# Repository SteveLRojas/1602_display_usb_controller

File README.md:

# 1602_display_usb_controller
Small controller board for 1602, 2004 and similar displays. It is intended to be controlled by a python script.

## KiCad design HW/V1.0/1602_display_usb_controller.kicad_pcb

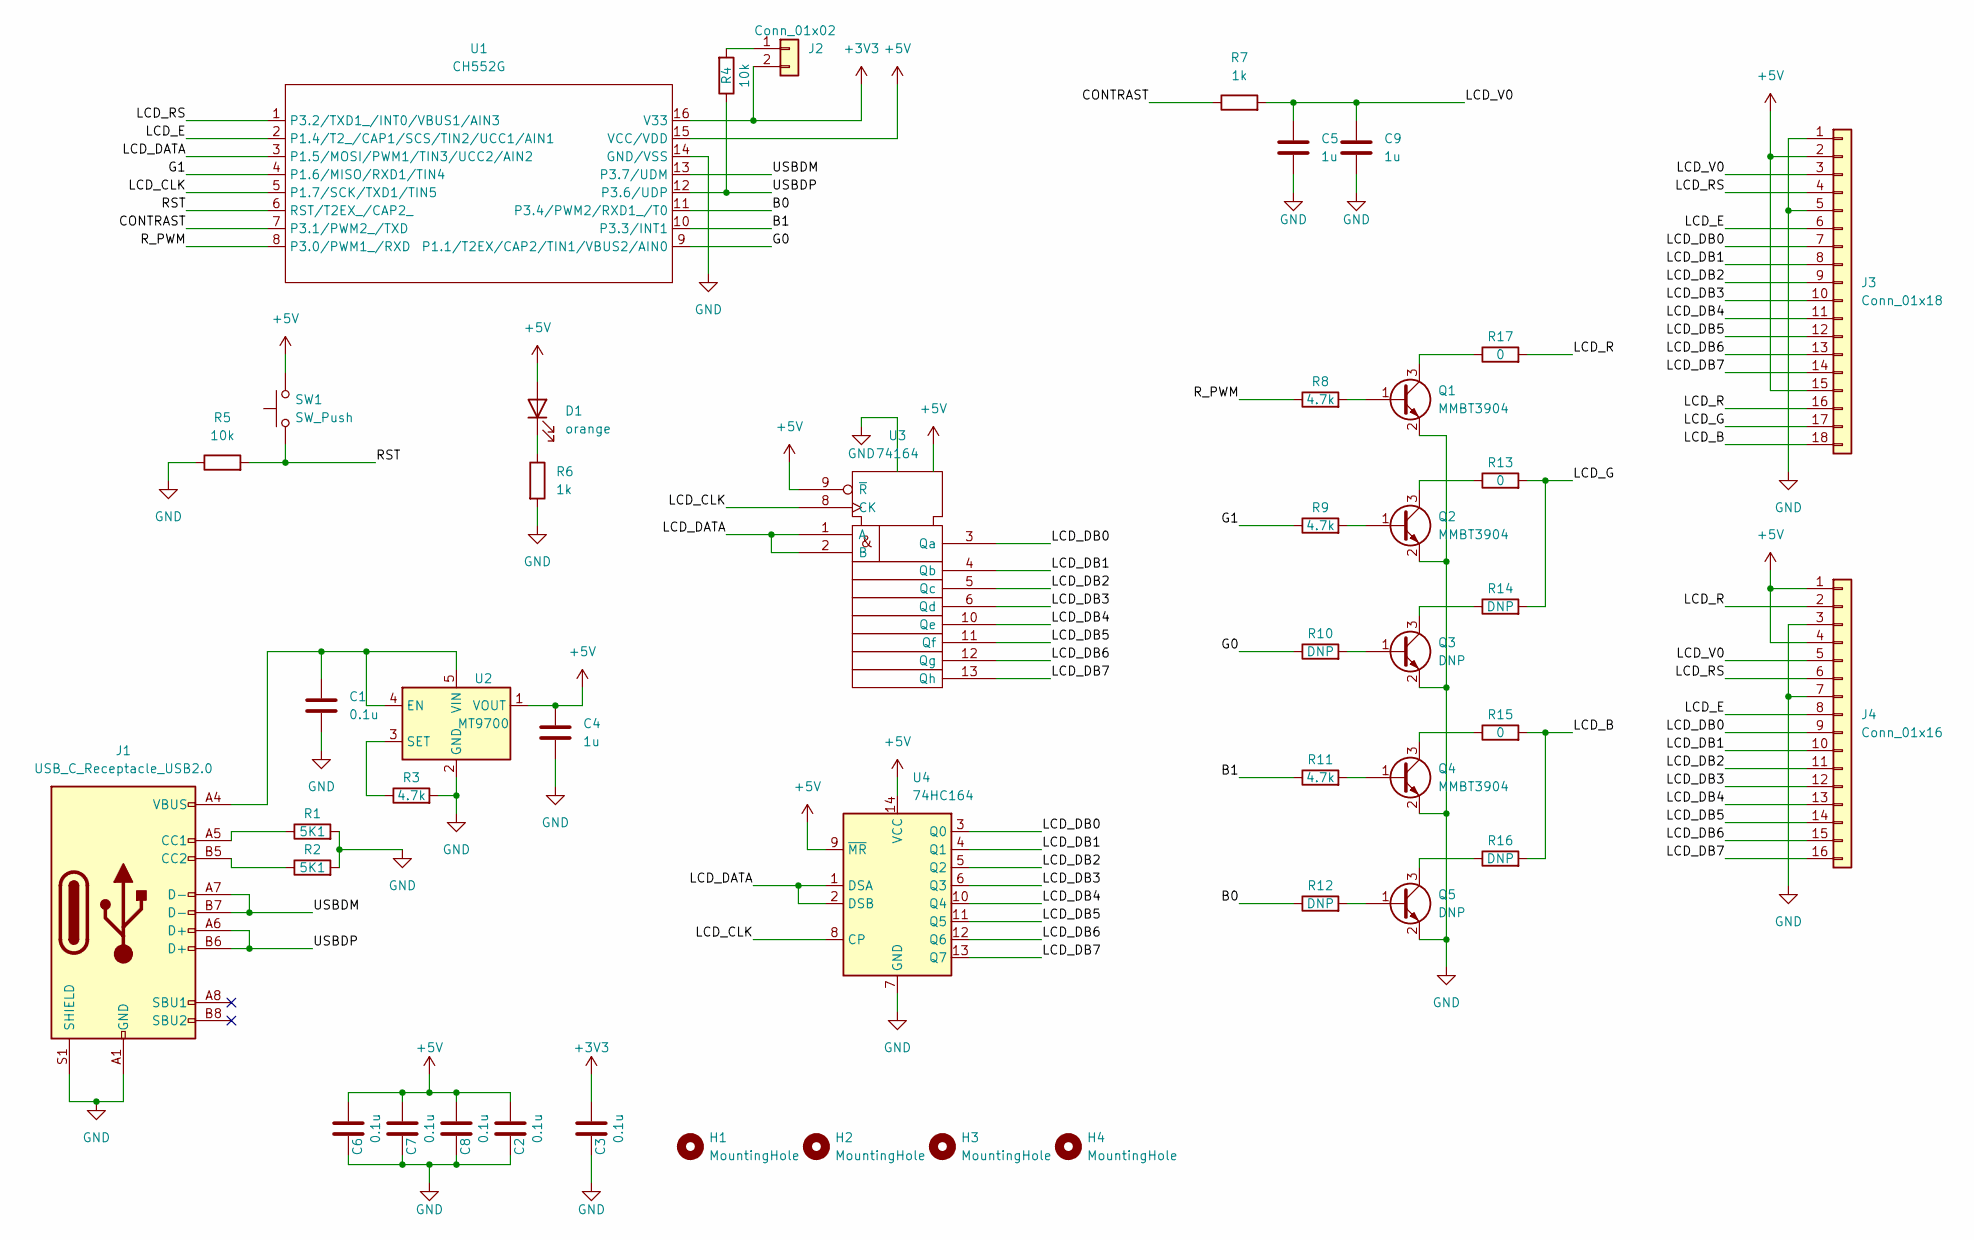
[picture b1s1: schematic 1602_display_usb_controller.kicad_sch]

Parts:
C1, C2, C3, C6, C7, C8: 0.1u; C_0805_2012Metric
C4, C5, C9: 1u; C_0805_2012Metric
D1: orange; LED_0805_2012Metric
H1, H2, H3, H4: MountingHole; MountingHole_2.5mm
J1: USB_C_Receptacle_USB2.0; USB_C_Receptacle_HRO_TYPE-C-31-M-12
J2: Conn_01x02; PinHeader_1x02_P1.27mm_Vertical
J3: Conn_01x18; PinSocket_1x18_P2.54mm_Vertical
J4: Conn_01x16; PinSocket_1x16_P2.54mm_Vertical
Q1, Q2, Q4: MMBT3904; SOT-23
Q3, Q5: DNP; SOT-23
R1, R2: 5K1; R_0805_2012Metric
R3, R8, R9, R11: 4.7k; R_0805_2012Metric
R4, R5: 10k; R_0805_2012Metric
R6, R7: 1k; R_0805_2012Metric
R10, R12, R14, R16: DNP; R_0805_2012Metric
R13, R15, R17: 0; R_0805_2012Metric
SW1: SW_Push; SW_SPST_PTS810
U1: CH552G; SO-16_3.9x9.9mm_P1.27mm
U2: MT9700; SOT-23-5
U3: 74164; DIP-14_W7.62mm
U4: 74HC164; SO-14_3.9x8.65mm_P1.27mm

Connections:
+3V3: C3.1, J2.2, U1.16 (V33)
+5V: C2.1, C4.1, C6.1, C7.1, C8.1, D1.2 (A), J3.2, J3.15, J4.1, J4.4, SW1.2, U1.15 (VCC/VDD), U2.1 (VOUT), U3.9 (~R), U3.14 (Vdd), U4.9 (~MR), U4.14 (VCC)
/B0: R12.1, U1.11 (P3.4/PWM2/RXD1_/T0)
/B1: R11.1, U1.10 (P3.3/INT1)
/CONTRAST: R7.1, U1.7 (P3.1/PWM2_/TXD)
/G0: R10.1, U1.9 (P1.1/T2EX/CAP2/TIN1/VBUS2/AIN0)
/G1: R9.1, U1.4 (P1.6/MISO/RXD1/TIN4)
/LCD_B: J3.18, R15.2, R16.2
/LCD_CLK: U1.5 (P1.7/SCK/TXD1/TIN5), U3.8 (CK), U4.8 (CP)
/LCD_DATA: U1.3 (P1.5/MOSI/PWM1/TIN3/UCC2/AIN2), U3.1 (A), U3.2 (B), U4.1 (DSA), U4.2 (DSB)
/LCD_DB0: J3.7, J4.9, U3.3 (Qa), U4.3 (Q0)
/LCD_DB1: J3.8, J4.10, U3.4 (Qb), U4.4 (Q1)
/LCD_DB2: J3.9, J4.11, U3.5 (Qc), U4.5 (Q2)
/LCD_DB3: J3.10, J4.12, U3.6 (Qd), U4.6 (Q3)
/LCD_DB4: J3.11, J4.13, U3.10 (Qe), U4.10 (Q4)
/LCD_DB5: J3.12, J4.14, U3.11 (Qf), U4.11 (Q5)
/LCD_DB6: J3.13, J4.15, U3.12 (Qg), U4.12 (Q6)
/LCD_DB7: J3.14, J4.16, U3.13 (Qh), U4.13 (Q7)
/LCD_E: J3.6, J4.8, U1.2 (P1.4/T2_/CAP1/SCS/TIN2/UCC1/AIN1)
/LCD_G: J3.17, R13.2, R14.2
/LCD_R: J3.16, J4.2, R17.2
/LCD_RS: J3.4, J4.6, U1.1 (P3.2/TXD1_/INT0/VBUS1/AIN3)
/LCD_V0: C5.1, C9.1, J3.3, J4.5, R7.2
/RST: R5.2, SW1.1, U1.6 (RST/T2EX_/CAP2_)
/R_PWM: R8.1, U1.8 (P3.0/PWM1_/RXD)
/USBDM: J1.A7 (D-), J1.B7 (D-), U1.13 (P3.7/UDM)
/USBDP: J1.A6 (D+), J1.B6 (D+), R4.1, U1.12 (P3.6/UDP)
GND: C1.2, C2.2, C3.2, C4.2, C5.2, C6.2, C7.2, C8.2, C9.2, J1.A1 (GND), J1.A12 (GND), J1.B1 (GND), J1.B12 (GND), J1.S1 (SHIELD), J3.1, J3.5, J4.3, J4.7, Q1.2 (E), Q2.2 (E), Q3.2 (E), Q4.2 (E), Q5.2 (E), R1.2, R2.2, R3.2, R5.1, R6.2, U1.14 (GND/VSS), U2.2 (GND), U3.7 (Vss), U4.7 (GND)
unnamed: C1.1, J1.A4 (VBUS), J1.A9 (VBUS), J1.B4 (VBUS), J1.B9 (VBUS), U2.4 (EN), U2.5 (VIN)
unnamed: D1.1 (K), R6.1
unnamed: J1.A5 (CC1), R1.1
unnamed: J1.B5 (CC2), R2.1
unnamed: J2.1, R4.2
unnamed: Q1.1 (B), R8.2
unnamed: Q1.3 (C), R17.1
unnamed: Q2.1 (B), R9.2
unnamed: Q2.3 (C), R13.1
unnamed: Q3.1 (B), R10.2
unnamed: Q3.3 (C), R14.1
unnamed: Q4.1 (B), R11.2
unnamed: Q4.3 (C), R15.1
unnamed: Q5.1 (B), R12.2
unnamed: Q5.3 (C), R16.1
unnamed: R3.1, U2.3 (SET)

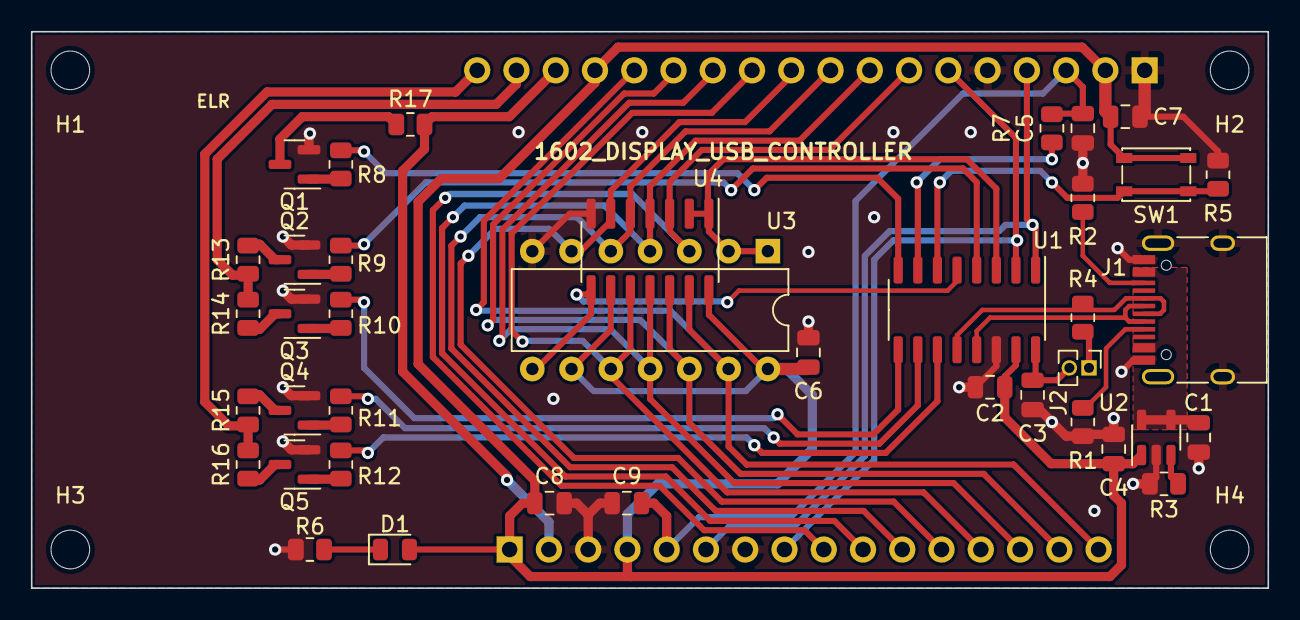
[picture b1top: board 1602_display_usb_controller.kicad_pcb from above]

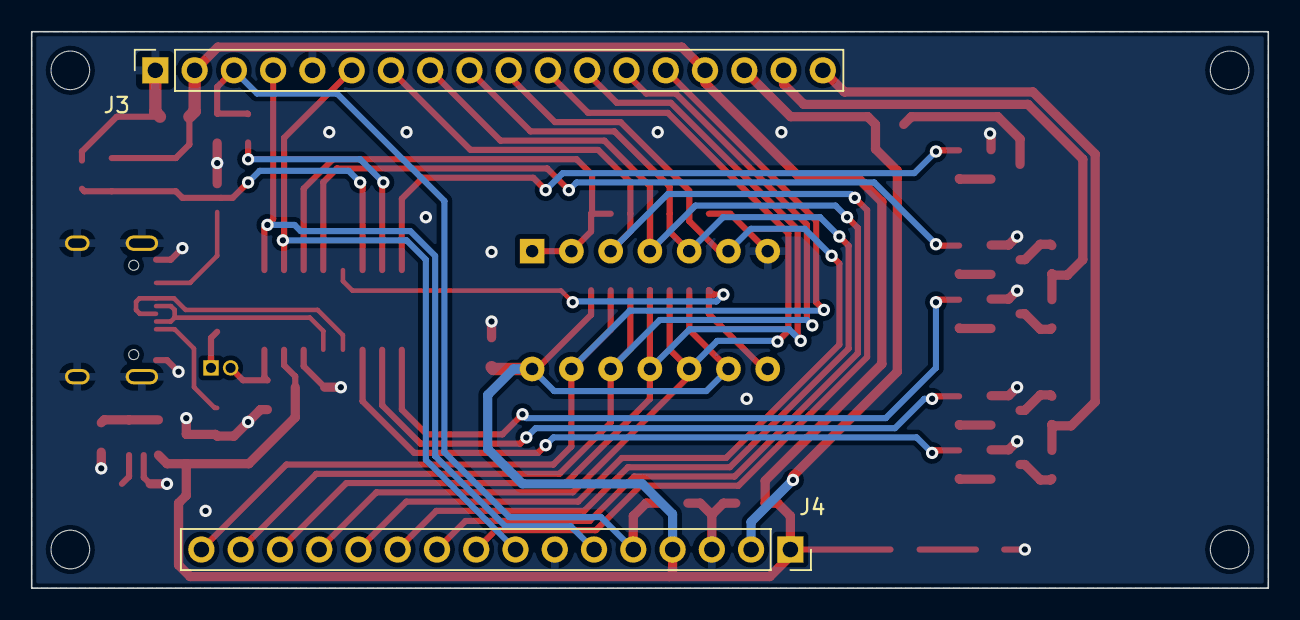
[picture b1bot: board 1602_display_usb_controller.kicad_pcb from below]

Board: 2 copper layers, 80.0 x 36.0 mm, 45 parts (2 on the bottom side), 44 nets.

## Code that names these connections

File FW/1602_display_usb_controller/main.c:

#include "CH552.H"
#include "CH552_RCC.h"
#include "CH552_TIMER.h"
#include "CH552_GPIO.h"
#include "CH552_PWM.h"
#include "CH552_USB_CDC.h"
#include "CH552_ST7066.h"

//Pins:
// LCD_E = P14
// LCD_DATA = P15
// G_PWM = P16
// LCD_CLK = P17
// R_PWM = P30
// LCD_CONTRAST = P31
// LCD_RS = P32
// B_PWM = P33
// UDP = P36
// UDM = P37

//PWM1 -> R_PWM
//PWM2 -> CONTRAST

int main()
{
	UINT8 prev_reset_typ;
	UINT16 com_wdog_count = 0;
	UINT16 com_wdog_limit = 0;
	
	UINT8 prev_control_line_state;
	UINT8 datagram[2];
	UINT16 bytes_available;
	UINT8 temp;
	UINT8 pwm_count = 0x08;
	
	UINT8 cursor_col = 0;
	UINT8 cursor_row = 0;
	UINT8 contrast = 45;
	UINT8 brightness_r = 127;
	UINT8 brightness_g = 127;
	UINT8 brightness_b = 127;
	UINT8 power_state = ST7066_DISP_ON_OFF_DISP_ON;
	
	rcc_set_clk_freq(RCC_CLK_FREQ_24M);
	
	gpio_set_mode(GPIO_MODE_PP, GPIO_PORT_1, GPIO_PIN_4 | GPIO_PIN_5 | GPIO_PIN_6 |GPIO_PIN_7);	//LCD_E, LCD_DATA, G_PWM, LCD_CLK
	gpio_set_mode(GPIO_MODE_PP, GPIO_PORT_3, GPIO_PIN_0 | GPIO_PIN_1 | GPIO_PIN_2 | GPIO_PIN_3);	//R_PWM, LCD_CONTRAST, LCD_RS, B_PWM
	gpio_clear_pin(GPIO_PORT_1, GPIO_PIN_4);
	gpio_clear_pin(GPIO_PORT_3, GPIO_PIN_2);
	
	pwm_init(PWM_1 | PWM_2, PWM_ACTIVE_HIGH, 1, PWM_1_P30 | PWM_2_P31);
	pwm_set_duty_cycle(PWM_1, brightness_r);
	pwm_set_duty_cycle(PWM_2, contrast);
	timer_init(TIMER_0, NULL);
	timer_set_period(TIMER_0, FREQ_SYS / 1000ul);	//period is 1ms
	EA = 1;	//enable interupts
	E_DIS = 0;
	
	prev_reset_typ = RESET_KEEP;
	RESET_KEEP = rcc_get_rst_typ();
	if((RESET_KEEP == RCC_RST_TYP_WDOG) || (RESET_KEEP == RCC_RST_TYP_SOFT))
	{
		rcc_delay_ms(500);
	}
	else
	{
		rcc_delay_ms(15);	//needed for some display modules
	}
	
	st7066_init();
	
	cdc_init();
	cdc_set_serial_state(CDC_SS_TXCARRIER | CDC_SS_RXCARRIER);
	prev_control_line_state = cdc_control_line_state;
	while(!cdc_config);
	
	timer_start(TIMER_0);
	
	rcc_reload_wdog(0x00);
	rcc_set_wdog_rst_en(RCC_WDOG_ENABLED);
	
	while(TRUE)
	{
		bytes_available = cdc_bytes_available();
		temp = cdc_peek();
		if((bytes_available >= 2) && (temp & 0x80))	//Handle write datagram
		{
			cdc_read_bytes(datagram, 2);
			
			switch(datagram[0] & 0x7F)
			{
				case 0x0A:
					cursor_col = datagram[1];
					st7066_set_cursor(cursor_row, cursor_col);
					break;
				case 0x0B:
					cursor_row = datagram[1];
					st7066_set_cursor(cursor_row, cursor_col);
					break;
				
				case 0x0C:
					contrast = datagram[1];
					pwm_set_duty_cycle(PWM_2, contrast);
					break;
				case 0x0D:
					brightness_r = datagram[1];
					pwm_set_duty_cycle(PWM_1, brightness_r);
					break;
				case 0x0E:
					brightness_g = datagram[1];
					break;
				case 0x0F:
					brightness_b = datagram[1];
					break;
				
				case 0x10:
					st7066_init();
					cursor_col = 0;
					cursor_row = 0;
					break;
				case 0x11:
					st7066_clear_display();
					cursor_col = 0;
					cursor_row = 0;
					break;
				case 0x12:
					cursor_col = 0;
					cursor_row = datagram[1];
					st7066_clear_line(cursor_row);
					break;
				case 0x13:
					st7066_write_char(datagram[1]);
					cursor_col += 1;
					break;
				
				case 0x14:
					power_state = datagram[1] & (ST7066_DISP_ON_OFF_DISP_ON | ST7066_DISP_ON_OFF_CURS_ON | ST7066_DISP_ON_OFF_BLINK_ON);
					st7066_send_command(ST7066_COM_DISP_ON_OFF | power_state);
					break;
				case 0x16:
					com_wdog_limit &= 0xFF00;
					com_wdog_limit |= datagram[1];
					break;
				case 0x17:
					com_wdog_limit &= 0x00FF;
					com_wdog_limit |= ((UINT16)datagram[1]) << 8;
					break;
				default: ;
			}
			
			com_wdog_count = 0;
		}
		else if(bytes_available && !(temp & 0x80))	//handle read datagram
		{
			datagram[0] = cdc_read_byte();
			
			switch(datagram[0])
			{
				case 0x00:	//device_id[0]
					datagram[0] = '1';
					break;
				case 0x01:	//device_id[1]
					datagram[0] = '6';
					break;
				case 0x02:	//device_id[2]
					datagram[0] = '0';
					break;
				case 0x03:	//device_id[3]
					datagram[0] = '2';
					break;
				
				case 0x04:	//unique_id[0]
					datagram[0] = (UINT8)(*(UINT16 code*)ROM_CHIP_ID_LO);
					break;
				case 0x05:	//unique_id[1]
					datagram[0] = (UINT8)((*(UINT16 code*)ROM_CHIP_ID_LO) >> 8);
					break;
				case 0x06:	//unique_id[2]
					datagram[0] = (UINT8)(*(UINT16 code*)ROM_CHIP_ID_HI);
					break;
				case 0x07:	//unique_id[3]
					datagram[0] = (UINT8)((*(UINT16 code*)ROM_CHIP_ID_HI) >> 8);
					break;
				
				case 0x08:
					datagram[0] = ST7066_NUM_COLUMNS;
					break;
				case 0x09:
					datagram[0] = ST7066_NUM_ROWS;
					break;
				case 0x0A:
					datagram[0] = cursor_col;
					break;
				case 0x0B:
					datagram[0] = cursor_row;
					break;
				
				case 0x0C:
					datagram[0] = contrast;
					break;
				case 0x0D:
					datagram[0] = brightness_r;
					break;
				case 0x0E:
					datagram[0] = brightness_g;
					break;
				case 0x0F:
					datagram[0] = brightness_b;
					break;
				
				case 0x14:
					datagram[0] = power_state;
					break;
				case 0x15:
					datagram[0] = prev_reset_typ | (RESET_KEEP >> 4);
					break;
				case 0x16:
					datagram[0] = (UINT8)com_wdog_limit;
					break;
				case 0x17:
					datagram[0] = (UINT8)(com_wdog_limit >> 8);
				default: ;
			}
			
			cdc_write_byte(datagram[0]);
			com_wdog_count = 0;
		}
		else if(bytes_available)	//datagrams not received in a single transfer are ignored
		{
			cdc_read_bytes(datagram, bytes_available);	//get rid of the extra bytes
		}
		
		if(com_wdog_limit && com_wdog_limit == com_wdog_count)
		{
			rcc_soft_reset();
		}
		
		if(timer_overflow_counts[TIMER_0])
		{
			timer_overflow_counts[TIMER_0] = 0;
			
			if(brightness_g >= pwm_count)
				gpio_set_pin(GPIO_PORT_1, GPIO_PIN_6);
			else
				gpio_clear_pin(GPIO_PORT_1, GPIO_PIN_6);
			
			if(brightness_b >= pwm_count)
				gpio_set_pin(GPIO_PORT_3, GPIO_PIN_3);
			else
				gpio_clear_pin(GPIO_PORT_3, GPIO_PIN_3);
			
			pwm_count += 0x10;
			com_wdog_count += 1;
		}
		
		if(prev_control_line_state != cdc_control_line_state)
		{
			cdc_set_serial_state(cdc_control_line_state & 3);
			prev_control_line_state = cdc_control_line_state;
		}
		
		rcc_reload_wdog(0x00);
	}
}

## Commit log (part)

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2026-03-12 Added design files
2026-03-17 Fixed CDC bug, added com watchdog, improvements in python files
2026-03-20 Added python scripts
2026-03-21 Added test scripts
2026-05-18 Added cpu and mem usage script
2026-06-07 Updated CDC library
2026-06-17 initialize display before USB
